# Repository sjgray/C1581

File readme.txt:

1581 ENHANCED PROJECT - Steve J. Gray
=====================

These are reproductions of the C1581 Disk Drive PCB.
The goal of this is to create enhanced PCBs which
can be modified, ie: reduced area for mounting 
inside a computer, increased ROM capacity, power
options, or laptop drive support, etc.

Enhancements:
- Jumpers for 1581/Amiga or PC drive.
- Jumpers for drive select 0 or 1.
- SkinnyDIP RAM chip.
- Double-size ROM with select (Standard or JiffyDOW).
- Optional header for 12V+5V internal power.
- Optional Barrel Jack for 12V power.
- Long pads for easier soldering.

ENHANCED
--------

This is a version with the same layout as the original,
with all original features and ports, plus all
enhancements. It can be installed in an original or
reproduction case. It includes the breakaway LED board.
It can also be powered with a 12V supply by replacing
the original 4-PIN DIN with the barrel jack.

INTERNAL
--------

This is a compact version with a slightly arranged
layout to pack the chips closer together. It removes
the DIN connectors, and LED breakaway.

*****************************************************
** The schematics and PCBs have NOT been verified! **
** Use at own risk!                                **
*****************************************************

Steve

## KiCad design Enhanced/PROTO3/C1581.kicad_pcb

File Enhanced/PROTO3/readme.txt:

1581 ENHANCED VERSION - PROTO 2
===============================

This is a reproduction of the C1541 Disk Drive PCB.
The goal of this is to create an enhanced PCB which
can be modified, ie: reduced area for mounting 
inside a computer.

Enhancements:
- Jumpers for 1581/Amiga or PC drive.
- Jumpers for drive select 0 or 1.
- SkinnyDIP RAM chip.
- Double-size ROM with select (Standard or JiffyDOW).
- Optional header for 12V+5V internal power.
- Optional Barrel Jack for 12V power.
- Long pads for easier soldering.

*********************************************
*** DESIGN NOT VERIFIED! USE AT OWN RISK! ***
*********************************************

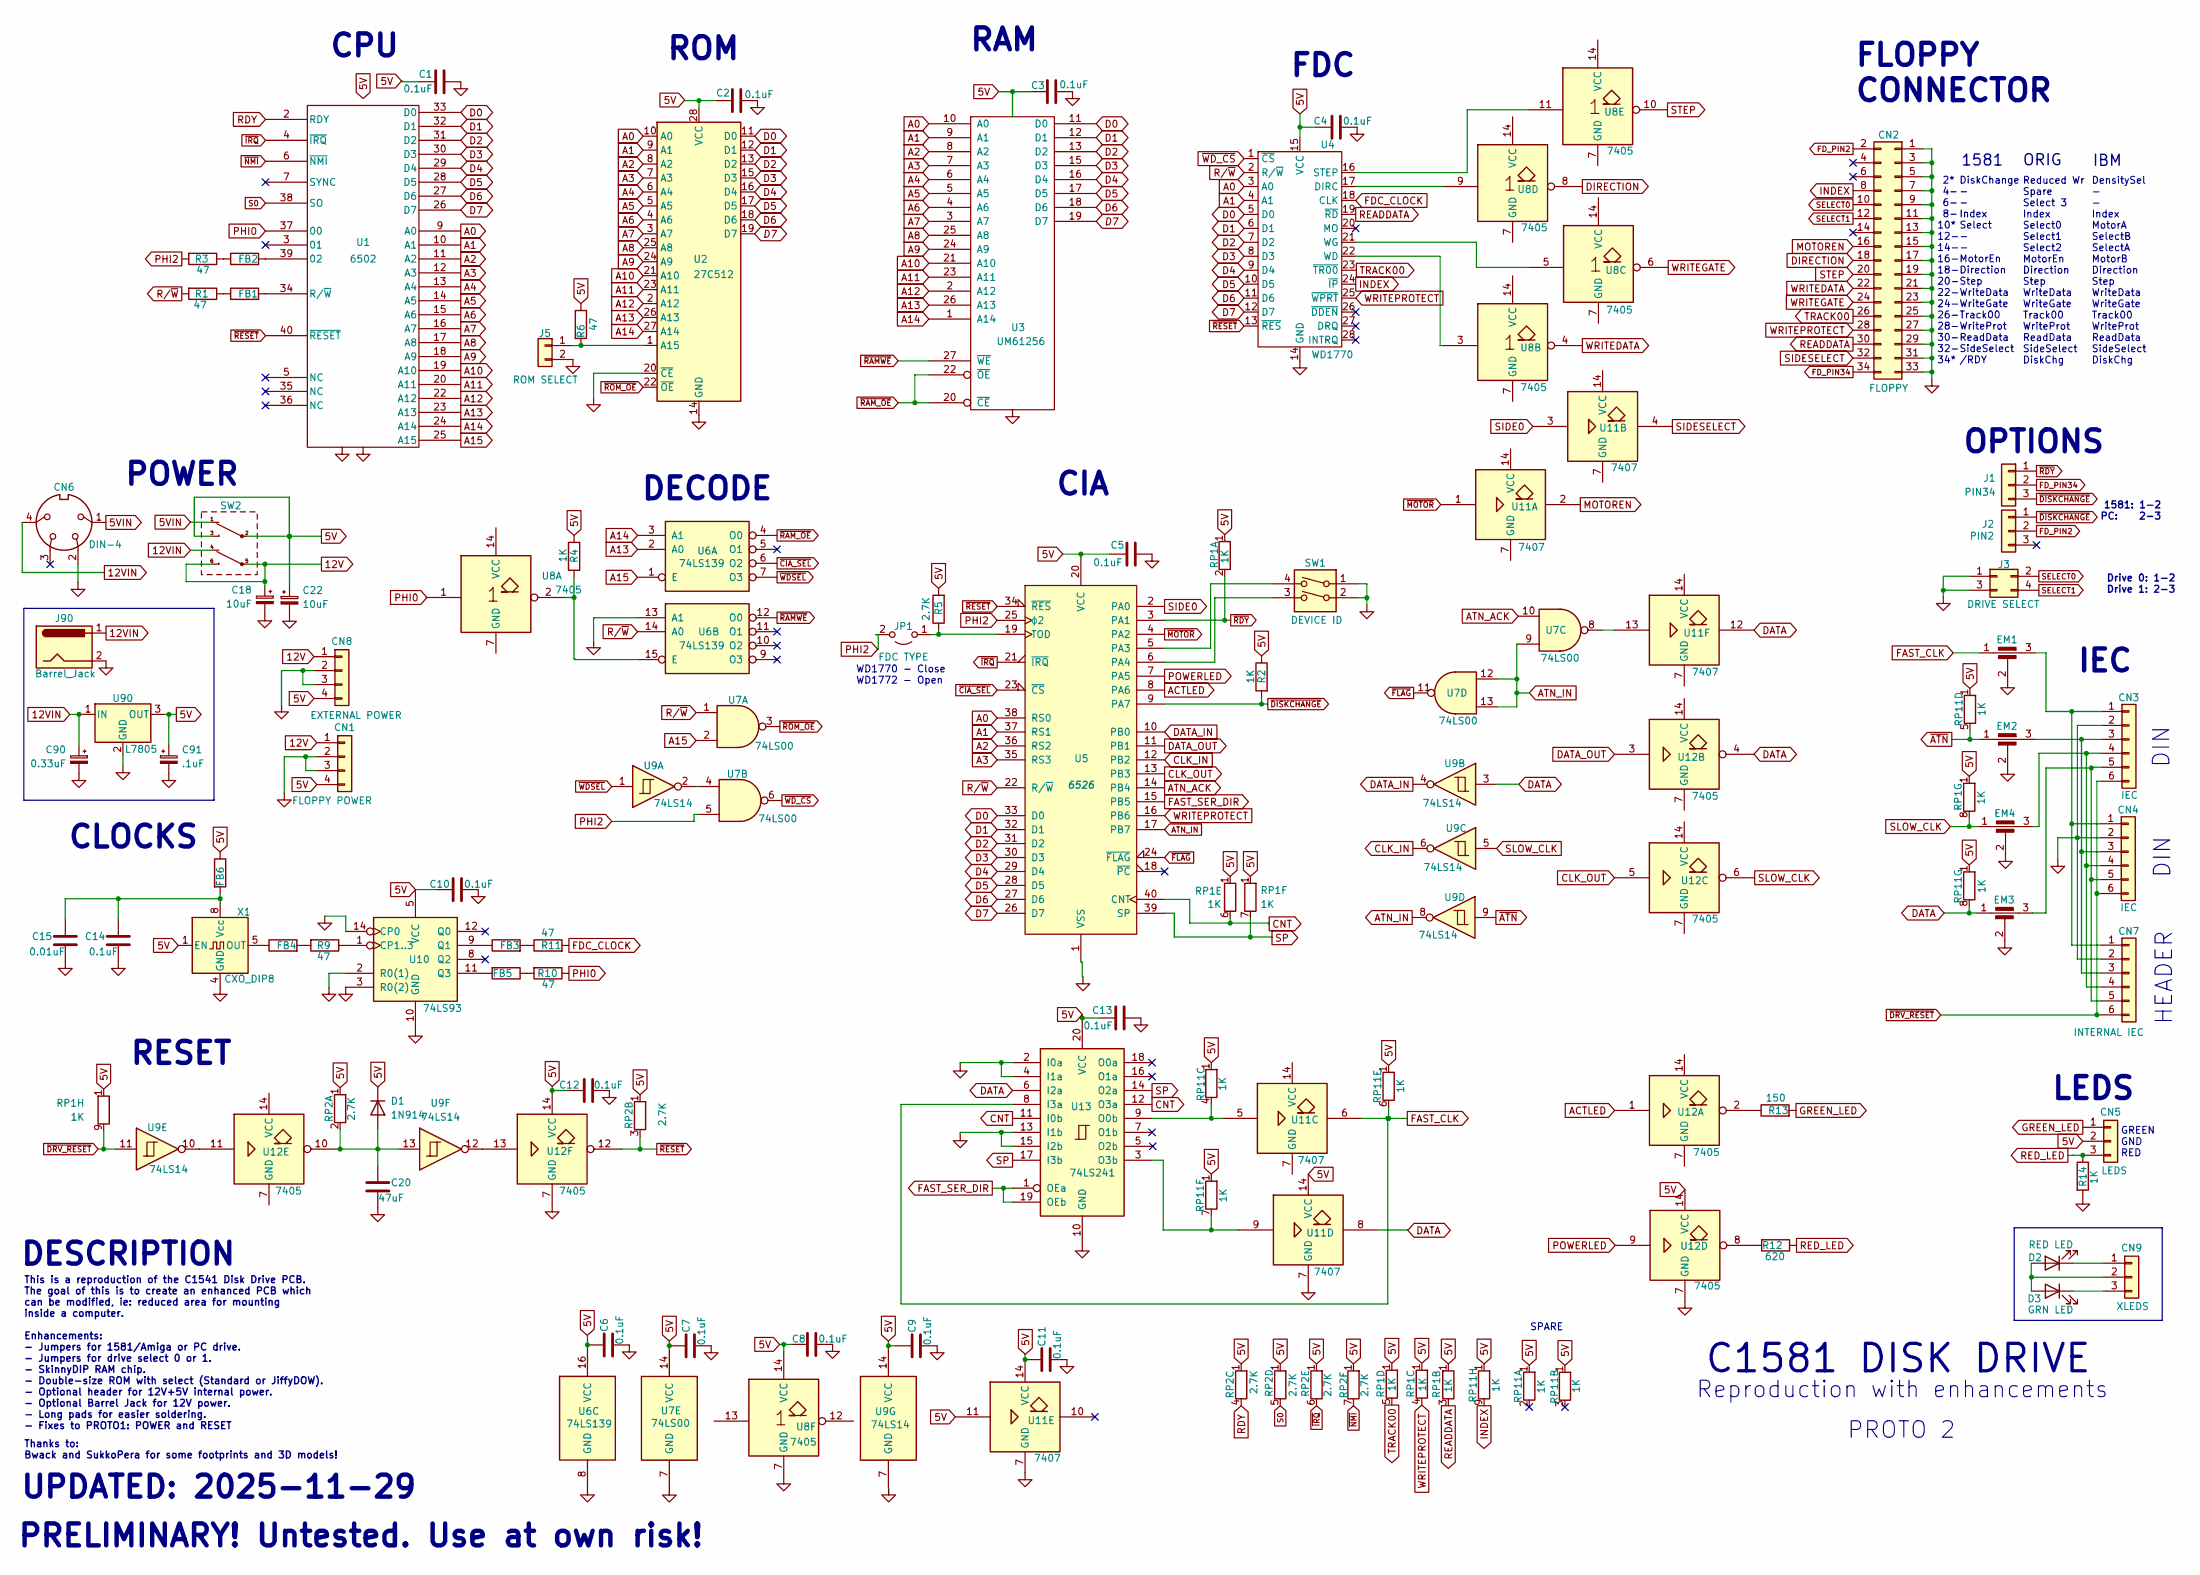
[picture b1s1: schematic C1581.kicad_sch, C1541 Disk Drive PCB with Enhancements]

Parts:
C1, C2, C3, C4, C5, C6, C7, C8, C9, C10, C11, C12, C13, C14: 0.1uF; C_Disc_D4.3mm_W1.9mm_P5.00mm
C15: 0.01uF; C_Disc_D4.3mm_W1.9mm_P5.00mm
C18, C22: 10uF; CAP_RADIAL_P5.08MM_D6MM
C20: 47uF; CAP_RADIAL_P5.08MM_D6MM
C90: 0.33uF; CAP_RADIAL_P5.08MM_D6MM
C91: .1uF; CAP_RADIAL_P5.08MM_D6MM
CN1: FLOPPY POWER; PinHeader_1x04_P2.54mm_Vertical
CN2: FLOPPY; PinHeader_2x17_P2.54mm_Vertical
CN3, CN4: IEC; SERIAL_CON_DIN6
CN5: LEDS; PinHeader_1x03_P2.54mm_Vertical
CN6: DIN-4
CN7: INTERNAL IEC; PinHeader_1x06_P2.54mm_Vertical
CN8: EXTERNAL POWER; PinHeader_1x04_P2.54mm_Vertical
CN9: XLEDS; PinHeader_1x03_P2.54mm_Vertical
D1: 1N914; D_DO-35_SOD27_P7.62mm_Horizontal
D2: RED LED; LED_D1.8mm_W3.3mm_H2.4mm
D3: GRN LED; LED_D1.8mm_W3.3mm_H2.4mm
EM1, EM2, EM3, EM4: 100pf; EMI_Filter
FB1, FB2, FB3, FB4, FB5, FB6: FB; R_Axial_DIN0309_L9.0mm_D3.2mm_P12.70mm_Horizontal
J1: PIN34; PinHeader_1x03_P2.54mm_Vertical
J2: PIN2; PinHeader_1x03_P2.54mm_Vertical
J3: DRIVE SELECT; PinHeader_2x02_P2.54mm_Vertical
J5: ROM SELECT; PinHeader_1x02_P2.54mm_Vertical
J90: Barrel_Jack; BarrelJack_Horizontal
JP1: FDC TYPE; PinHeader_1x02_P2.54mm_Vertical
R1, R3, R6, R9, R10, R11: 47; R_Axial_DIN0309_L9.0mm_D3.2mm_P12.70mm_Horizontal
R2, R4, R14: 1K; R_Axial_DIN0309_L9.0mm_D3.2mm_P12.70mm_Horizontal
R5: 2.7K; R_Axial_DIN0309_L9.0mm_D3.2mm_P12.70mm_Horizontal
R12: 620; R_Axial_DIN0309_L9.0mm_D3.2mm_P12.70mm_Horizontal
R13: 150; R_Axial_DIN0309_L9.0mm_D3.2mm_P12.70mm_Horizontal
RP1, RP11: 1K; R_Array_SIP9
RP2: 2.7K; R_Array_SIP8
SW1: DEVICE ID; SW_DIP_SPSTx02_Piano_10.8x6.64mm_W7.62mm_P2.54mm
SW2: C64_PowerSwitch
U1: 6502; DIP-40_W15.24mm_LongPads
U2: 27C512; DIP-28_W15.24mm
U3: UM61256; DIP-28_W7.62mm_LongPads
U4: WD1770; DIP-28_W15.24mm_LongPads
U5: 6526; DIP-40_W15.24mm_LongPads
U6: 74LS139; DIP-16_W7.62mm_LongPads
U7: 74LS00; DIP-14_W7.62mm_LongPads
U8, U12: 7405; DIP-14_W7.62mm_LongPads
U9: 74LS14; DIP-14_W7.62mm_LongPads
U10: 74LS93; DIP-14_W7.62mm_LongPads
U11: 7407; DIP-14_W7.62mm_LongPads
U13: 74LS241; DIP-20_W7.62mm_LongPads
U90: L7805; TO-220-3_Vertical
X1: CXO_DIP8; Oscillator_DIP-8

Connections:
5V: C1.1, C2.1, C3.1, C4.1, C5.1, C6.1, C7.1, C8.1, C9.1, C10.1, C11.1, C12.1, C13.1, C22.1, C91.1, CN1.4, CN5.2, CN8.4, D1.1 (K), FB6.1, R2.1, R4.2, R5.2, R6.1, RP1.1 (R1), RP2.1 (R1), RP11.1 (R1), SW2.2, SW2.3, U1.8 (Vcc), U2.28 (VCC), U3.28 (VCC), U4.15 (VCC), U5.20 (VCC), U6.16 (VCC), U7.14 (VCC), U8.14 (VCC), U9.14 (VCC), U10.5 (VCC), U11.11, U11.14 (VCC), U12.14 (VCC), U13.20 (VCC), U90.3 (OUT), X1.1 (EN)
5VIN: CN6.1, SW2.1
12V: C18.1, CN1.1, CN8.1, SW2.5, SW2.6
12VIN: C90.1, CN6.4, J90.1, SW2.4, U90.1 (IN)
A0: U1.9 (A0), U2.10 (A0), U3.10 (A0), U4.3 (A0), U5.38 (RS0)
A1: U1.10 (A1), U2.9 (A1), U3.9 (A1), U4.4 (A1), U5.37 (RS1)
A2: U1.11 (A2), U2.8 (A2), U3.8 (A2), U5.36 (RS2)
A3: U1.12 (A3), U2.7 (A3), U3.7 (A3), U5.35 (RS3)
A4: U1.13 (A4), U2.6 (A4), U3.6 (A4)
A5: U1.14 (A5), U2.5 (A5), U3.5 (A5)
A6: U1.15 (A6), U2.4 (A6), U3.4 (A6)
A7: U1.16 (A7), U2.3 (A7), U3.3 (A7)
A8: U1.17 (A8), U2.25 (A8), U3.25 (A8)
A9: U1.18 (A9), U2.24 (A9), U3.24 (A9)
A10: U1.19 (A10), U2.21 (A10), U3.21 (A10)
A11: U1.20 (A11), U2.23 (A11), U3.23 (A11)
A12: U1.22 (A12), U2.2 (A12), U3.2 (A12)
A13: U1.23 (A13), U2.26 (A13), U3.26 (A13), U6.2 (A0)
A14: U1.24 (A14), U2.27 (A14), U3.1 (A14), U6.3 (A1)
A15: U1.25 (A15), U6.1 (E), U7.2
ACTLED: U5.8 (PA6), U12.1
ATN_ACK: U5.14 (PB4), U7.10
ATN_IN: U5.17 (PB7), U7.9, U7.12, U7.13, U9.8
CLK_IN: U5.12 (PB2), U9.6
CLK_OUT: U5.13 (PB3), U12.5
CNT: RP1.6 (R5.2), U5.40 (CNT), U13.11 (I0b), U13.12 (O3a)
D0: U1.33 (D0), U2.11 (D0), U3.11 (D0), U4.5 (D0), U5.33 (D0)
D1: U1.32 (D1), U2.12 (D1), U3.12 (D1), U4.6 (D1), U5.32 (D1)
D2: U1.31 (D2), U2.13 (D2), U3.13 (D2), U4.7 (D2), U5.31 (D2)
D3: U1.30 (D3), U2.15 (D3), U3.15 (D3), U4.8 (D3), U5.30 (D3)
D4: U1.29 (D4), U2.16 (D4), U3.16 (D4), U4.9 (D4), U5.29 (D4)
D5: U1.28 (D5), U2.17 (D5), U3.17 (D5), U4.10 (D5), U5.28 (D5)
D6: U1.27 (D6), U2.18 (D6), U3.18 (D6), U4.11 (D6), U5.27 (D6)
D7: U1.26 (D7), U2.19 (D7), U3.19 (D7), U4.12 (D7), U5.26 (D7)
DATA: EM3.1, RP11.8 (R7.2), U9.3, U11.8, U11.12, U12.4, U13.6 (I2a)
DATA_IN: U5.10 (PB0), U9.4
DATA_OUT: U5.11 (PB1), U12.3
DIRECTION: CN2.18, U8.8
FAST_CLK: EM1.1, RP11.6 (R5.2), U11.6, U13.8 (I3a)
FAST_SER_DIR: U5.15 (PB5), U13.1 (OEa), U13.19 (OEb)
FDC_CLOCK: R11.2, U4.18 (CLK)
FD_PIN2: CN2.2, J2.2
FD_PIN34: CN2.34, J1.2
GND: C1.2, C2.2, C3.2, C4.2, C5.2, C6.2, C7.2, C8.2, C9.2, C10.2, C11.2, C12.2, C13.2, C14.2, C15.2, C18.2, C20.2, C22.2, C90.2, C91.2, CN1.2, CN1.3, CN2.1, CN2.3, CN2.5, CN2.7, CN2.9, CN2.11, CN2.13, CN2.15, CN2.17, CN2.19, CN2.21, CN2.23, CN2.25, CN2.27, CN2.29, CN2.31, CN2.33, CN3.2, CN4.2, CN6.2, CN7.2, CN8.2, CN8.3, EM1.2, EM2.2, EM3.2, EM4.2, J3.1, J3.3, J5.2, J90.2, R14.2, SW1.1, SW1.2, U1.1 (VSS), U1.21 (GND), U2.14 (GND), U2.20 (~CE), U3.14 (GND), U4.14 (GND), U5.1 (VSS), U6.8 (GND), U6.13 (A1), U7.7 (GND), U8.7 (GND), U9.7 (GND), U10.2 (R0(1)), U10.3 (R0(2)), U10.10 (GND), U10.14 (CP0), U11.7 (GND), U12.7 (GND), U13.2 (I0a), U13.4 (I1a), U13.10 (GND), U13.13 (I1b), U13.15 (I2b), U90.2 (GND), X1.4 (GND)
GREEN_LED: CN5.1, R13.2
INDEX: CN2.8, RP11.9 (R8.2), U4.24 (~IP)
MOTOREN: CN2.16, U11.2
unnamed: CN3.1, CN4.1, CN7.1, EM1.3
unnamed: CN3.3, CN4.3, CN7.3, EM2.3
unnamed: CN3.4, CN4.4, CN7.4, EM4.3
unnamed: CN3.5, CN4.5, CN7.5, EM3.3
unnamed: CN9.1, D2.1 (K)
unnamed: CN9.2, D2.2 (A), D3.2 (A)
unnamed: CN9.3, D3.1 (K)
unnamed: C20.1, D1.2 (A), RP2.2 (R1.2), U9.13, U12.10
unnamed: FB1.1, R1.1
unnamed: FB2.1, R3.1
unnamed: FB3.2, R11.1
unnamed: FB4.2, R9.2
unnamed: FB5.1, R10.2
unnamed: J5.1, R6.2, U2.1 (A15)
unnamed: JP1.1 (A), R5.1, U5.19 (TOD)
unnamed: R12.2, U12.8
unnamed: R13.1, U12.2
unnamed: RP11.4 (R3.2), U11.5, U13.9 (O0b)
unnamed: RP11.7 (R6.2), U11.9, U13.3 (O3b)
unnamed: FB2.2, U1.39 (02)
unnamed: FB1.2, U1.34 (R/~W)
unnamed: U4.17 (DIRC), U8.9
unnamed: U4.16 (STEP), U8.11
unnamed: U4.22 (WD), U8.3
unnamed: U4.21 (WG), U8.5
unnamed: SW1.4, U5.5 (PA3)
unnamed: SW1.3, U5.6 (PA4)
unnamed: R4.1, U6.15 (E), U8.2
unnamed: U7.4, U9.2
unnamed: R9.1, U10.1 (CP1..3)
unnamed: FB3.1, U10.9 (Q1)
unnamed: FB5.2, U10.11 (Q3)
unnamed: U7.8, U11.13
unnamed: U9.10, U12.11
unnamed: U9.12, U12.13
unnamed: FB4.1, X1.5 (OUT)
unnamed: C14.1, C15.1, FB6.2, X1.8 (Vcc)
PHI0: R10.1, U1.37 (00), U8.1
PHI2: JP1.2 (B), R3.2, U5.25 (ϕ2), U7.5
POWERLED: U5.7 (PA5), U12.9
RDY: RP2.4 (R3.2), U1.2 (RDY)
READDATA: CN2.30, RP1.3 (R2.2), U4.19 (~RD)
RED_LED: CN5.3, R12.1, R14.1
R/~W: R1.2, U4.2 (R/~W), U5.22 (R/~W), U6.14 (A0), U7.1
S0: RP2.5 (R4.2), U1.38 (SO)
SELECT0: CN2.10, J3.2
SELECT1: CN2.12, J3.4
SIDE0: U5.2 (PA0), U11.3
SIDESELECT: CN2.32, U11.4
SLOW_CLK: EM4.1, RP1.8 (R7.2), U9.5, U12.6
SP: RP1.7 (R6.2), U5.39 (SP), U13.14 (O2a), U13.17 (I3b)
STEP: CN2.20, U8.10
TRACK00: CN2.26, RP1.5 (R4.2), U4.23 (~TR00)
WRITEDATA: CN2.22, U8.4
WRITEGATE: CN2.24, U8.6
WRITEPROTECT: CN2.28, RP1.4 (R3.2), U4.25 (~WPRT), U5.16 (PB6)
~ATN: EM2.1, RP11.5 (R4.2), U9.9
~CIA_SEL: U5.23 (~CS), U6.6 (O2)
~DISKCHANGE: J1.3, J2.1, R2.2, U5.9 (PA7)
~DRV_RESET: CN3.6, CN4.6, CN7.6, RP1.9 (R8.2), U9.11
~FLAG: U5.24 (~FLAG), U7.11
~IRQ: RP2.6 (R5.2), U1.4 (~IRQ), U5.21 (~IRQ)
~MOTOR: U5.4 (PA2), U11.1
~NMI: RP2.7 (R6.2), U1.6 (~NMI)
~RAMWE: U3.27 (~WE), U6.12 (O0)
~RAM_OE: U3.20 (~CE), U3.22 (~OE), U6.4 (O0)
~RDY: J1.1, RP1.2 (R1.2), U5.3 (PA1)
~RESET: RP2.3 (R2.2), U1.40 (~RESET), U4.13 (~RES), U5.34 (~RES), U12.12
~ROM_OE: U2.22 (~OE), U7.3
~WDSEL: U6.7 (O3), U9.1
~WD_CS: U4.1 (~CS), U7.6

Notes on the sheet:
DECODE
UPDATED: 2025-11-29
ORIG
Drive 0: 1-2 Drive 1: 2-3
Reduced Wr Spare Select 3 Index Select0 Select1 Select2 MotorEn Direction Step WriteData WriteGate Track00 WriteProt ReadData SideSelect DiskChg
2* 4- 6- 8- 10* 12- 14- 16- 18- 20- 22- 24- 26- 28- 30- 32- 34*
DiskChange - - Index Select - - MotorEn Direction Step WriteData WriteGate Track00 WriteProt ReadData SideSelect /RDY
CLOCKS
POWER
ROM
DIN
HEADER
CIA
LEDS
RESET
DensitySel - - Index MotorA SelectB SelectA MotorB Direction Step WriteData WriteGate Track00 WriteProt ReadData SideSelect DiskChg
RAM
This is a reproduction of the C1541 Disk Drive PCB. The goal of this is to create an enhanced PCB which can be modified, ie: reduced area for mounting inside a computer. Enhancements: - Jumpers for 1581/Amiga or PC drive. - Jumpers for drive select 0 or 1. - SkinnyDIP RAM chip. - Double-size ROM wi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
FLOPPY CONNECTOR
1581
IBM
C1581 DISK DRIVE
CPU
PRELIMINARY! Untested. Use at own risk!
Thanks to: Bwack and SukkoPera for some footprints and 3D models!
1581: 1-2 PC: 2-3
DESCRIPTION
OPTIONS
GREEN GND RED
SPARE
FDC
Reproduction with enhancements
WD1770 - Close WD1772 - Open
IEC
PROTO 2

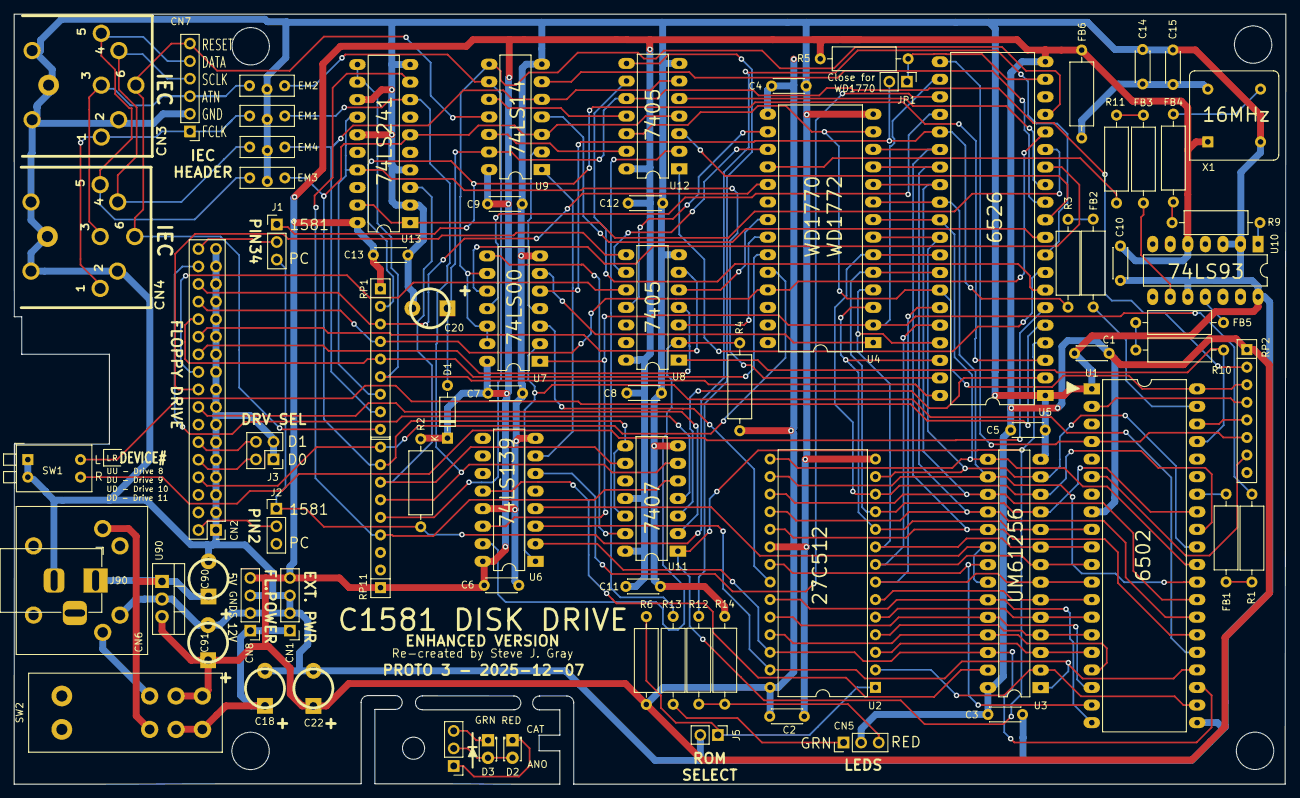
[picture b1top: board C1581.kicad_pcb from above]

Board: 2 copper layers, 183.9 x 111.3 mm, 80 parts (0 on the bottom side), 118 nets.

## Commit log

2024-02-07 Initial Design
    This is a 1581 disk drive PCB with enhancements, created in Kicad.
2024-02-08 Update to readme
    Update readme and fix some typos.
2024-02-08 Add 1581i Internal Version
    Smaller, for mounting inside a computer case. Removes DIN headers, and packs components closer together.
2024-02-08 Add readme
    Add Readme for both versions.
2024-02-08 fix typo
    fix typo.
2024-02-09 1581i Update
    Lots of re-routing to pack components tighter. PCB is now smaller. Added FPC connector to add Laptop PC drive support. Add board render.
2024-02-09 Floppy connector area updates
    Move floppy connector and jumpers. Add additional mounting holes.
2024-02-12 Add Enable/Disable Jumper
    Allows use of an external switch to enable/disable the drive.
2024-02-15 1581i - Fix 12v power
    Fix 12V from barrel jack not connecting to floppy power. I am making a small run of boards from JLCPCB to test the design.
2024-02-15 1581i - fix typo, update pdf and render
    Fix typo in description. Update schematic PDF and board render.
2024-05-07 Enhanced and Internal BOM
    Add interactive BOM
2025-09-17 Release PROTO 2
    Fixed reported errors with power missing from a couple chips, plus reset. Added improved labelling and trace optimization. Not tested by me. Use at own risk.
2025-09-17 Uppdate to PROTO2 files
    Updated PDF and board JPG
2025-09-17 Release Enhanced PROTO2
    With fixes to power and reset, and updated labelling.
2025-09-17 Update readme
    These designs are untested. Use at own risk. Gerbers are provided for those that would like to help or provide feedback to the project.
2025-11-30 Add EMI component values
    Add missing EMI component values and generated new Interactive BOMs for both Enhanced and Internal Proto2 designs.
2025-12-02 Add Internal Proto3
    Fixed trace to FPC, moved floppy connector to make more space for FPC cable
2025-12-08 Enhanced Proto#3
    Fix missing R5 trace. Update labels. Generate new gerbers.
